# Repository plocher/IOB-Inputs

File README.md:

# IOB-Inputs
## License: CERN Open Hardware Licence v1.2

1k series resistor protects from shorts to Vcc or GND

PNP Ready: Panelized IOB quad "input board", used for [IO4-QuodOD](/pages/IO4-QuadOD), [IO4-IR-Detector-Active](/pages/IO4-IR-Detector-Active), and [IO4-IR-Detector-GBunza](/pages/IO4-IR-Detector-GBunza) detectors as well as other IO4 sensor accessories that provide 4x lines of active-low digital feedback.

  * pin 1: 5vDC
  * pin 2: !IN1
  * pin 3: !IN2
  * pin 4: !IN3
  * pin 5: !IN4
  * pin 6: GND

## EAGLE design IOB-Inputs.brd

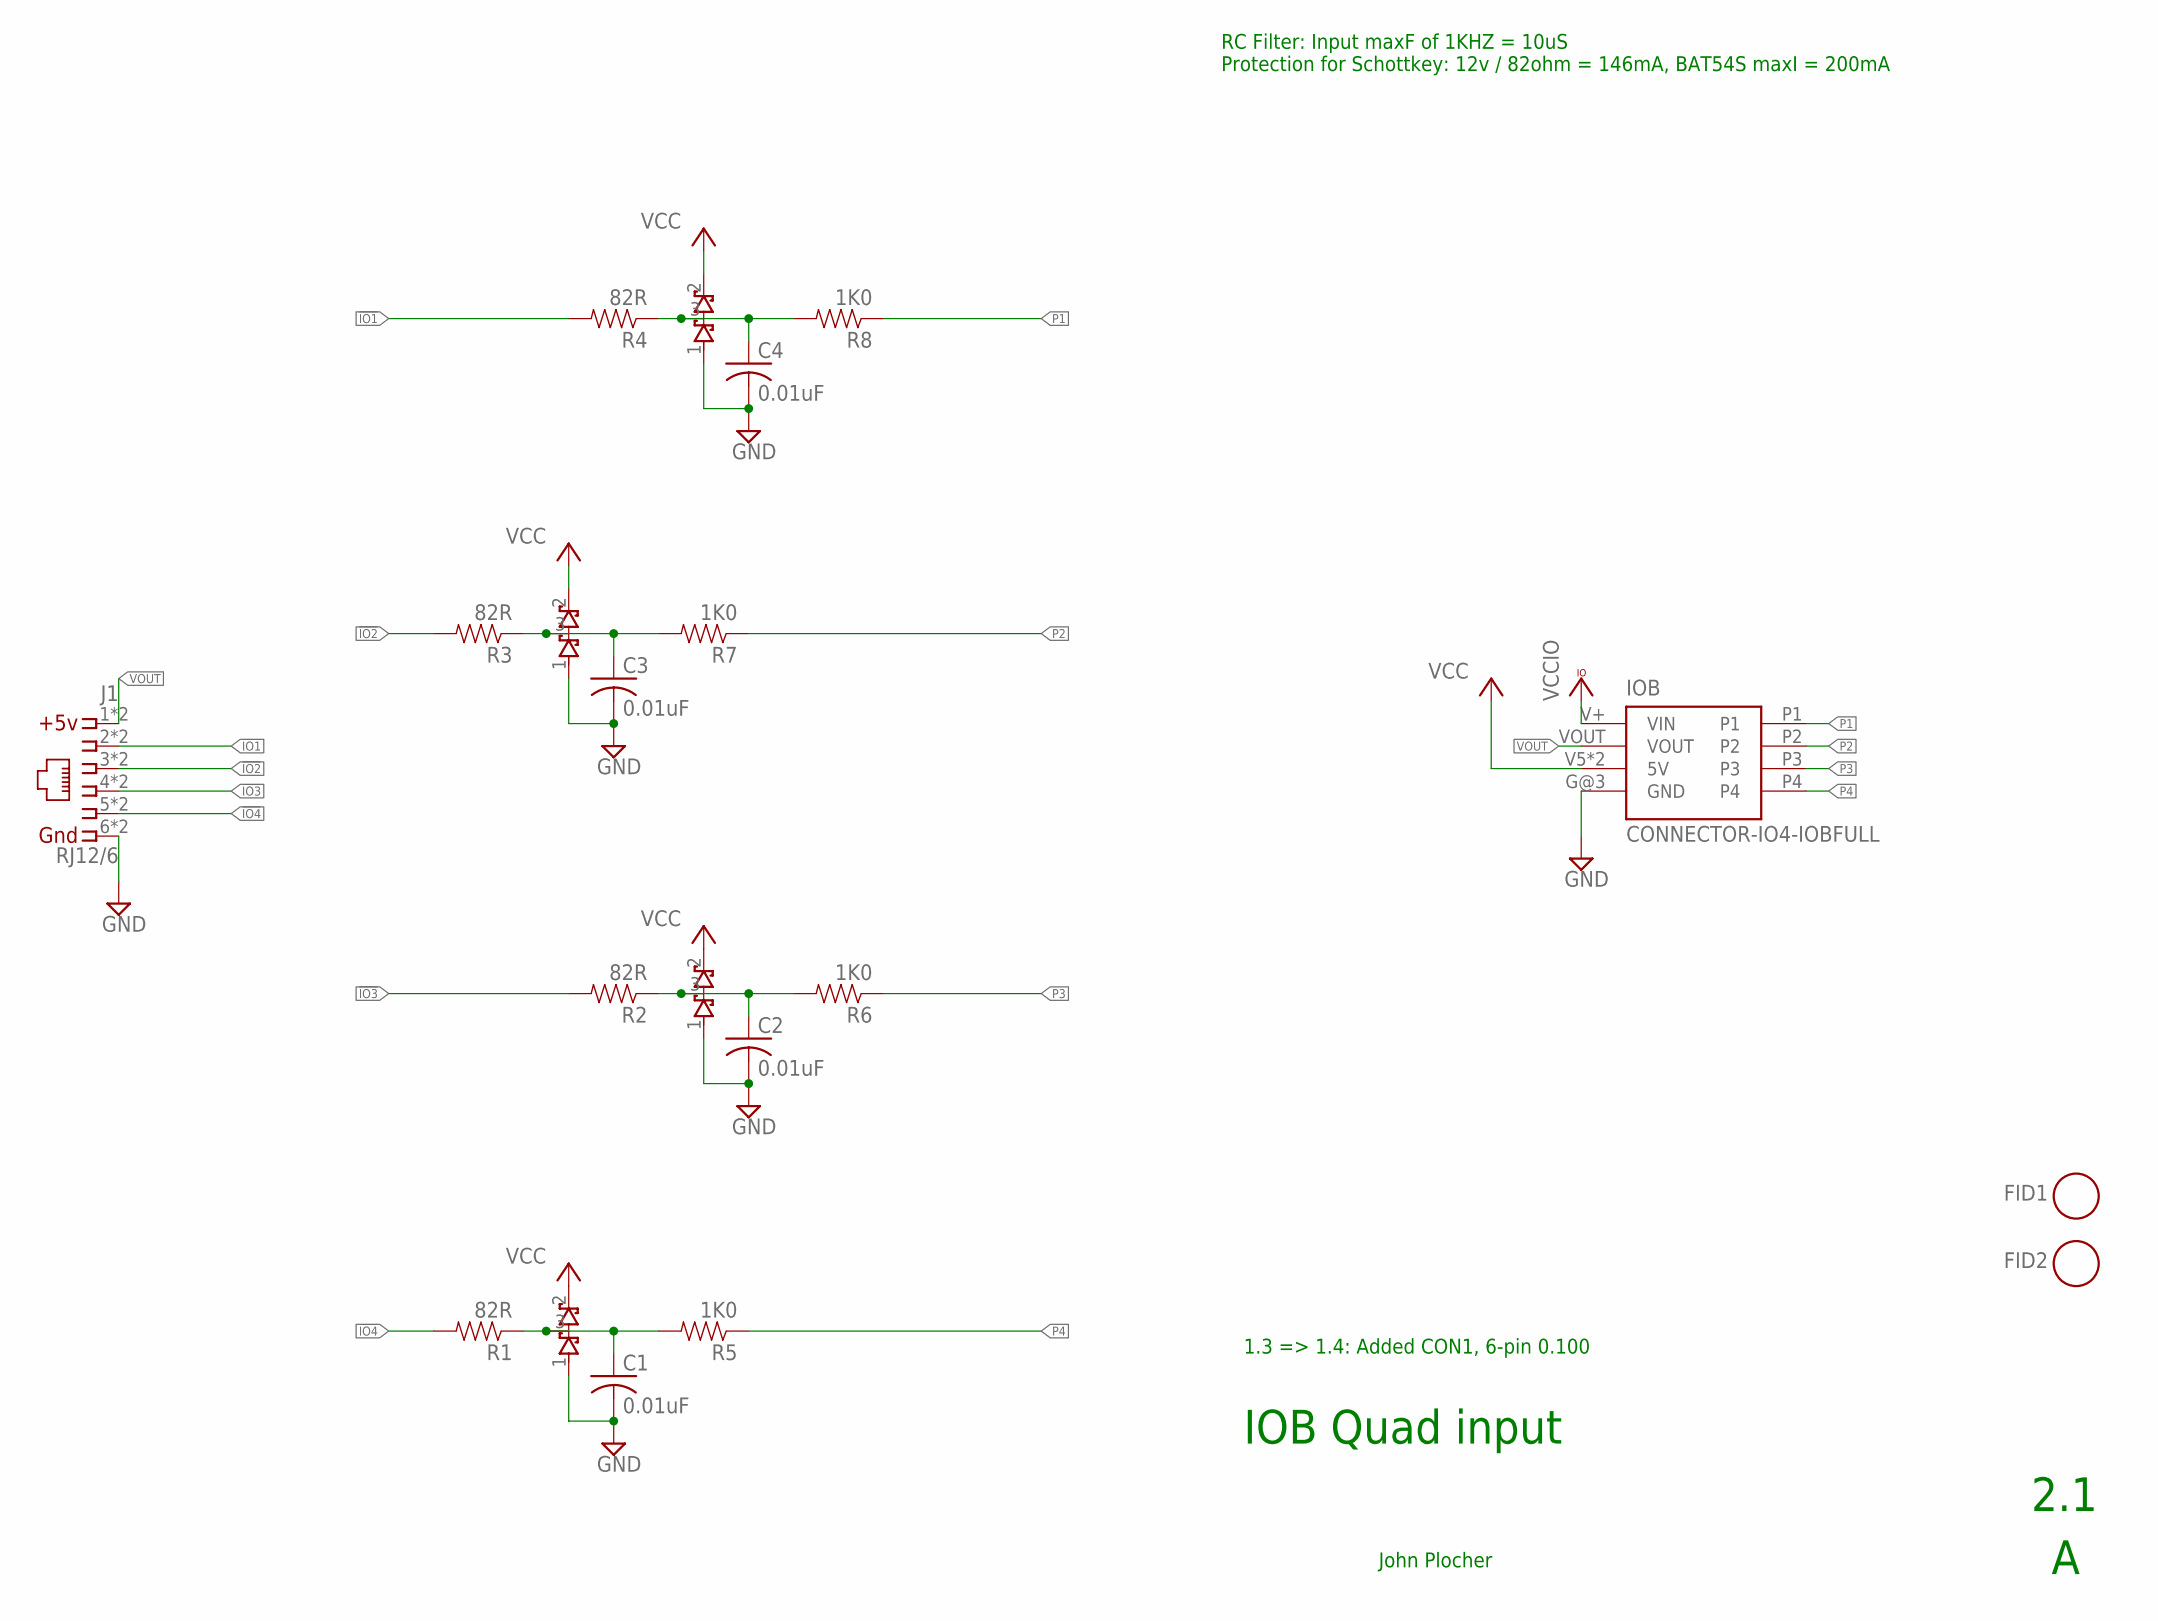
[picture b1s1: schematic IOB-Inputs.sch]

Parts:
C1, C2, C3, C4: 0.01uF; 0603-CAP
D1, D2, D3, D4: BAT54S; SOT23
FID1, FID2: FIDUCIAL; FIDUCIAL_1MM
IOB: CONNECTOR-IO4-IOBFULL; IO4-IOB
J1: RJ12/6; RJ24-INVERTED-PINS
R1, R2, R3, R4: 82R; 0805-RES
R5, R6, R7, R8: 1K0; 0603-RES

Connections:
!IO1: J1.2, J1.2@1 (2), R4.2
!IO2: J1.3, J1.3@1 (3), R3.2
!IO3: J1.4, J1.4@1 (4), R2.2
!IO4: J1.5, J1.5@1 (5), R1.2
GND: C1.2, C2.2, C3.2, C4.2, D1.1 (A1), D2.1 (A1), D3.1 (A1), D4.1 (A1), IOB.G@3 (GND), J1.6, J1.6@1 (6)
unnamed: C1.1, D1.3 (COM), R1.1, R5.2
unnamed: C2.1, D2.3 (COM), R2.1, R6.2
unnamed: C3.1, D3.3 (COM), R3.1, R7.2
unnamed: C4.1, D4.3 (COM), R4.1, R8.2
P1: IOB.P1, R8.1
P2: IOB.P2, R7.1
P3: IOB.P3, R6.1
P4: IOB.P4, R5.1
VCC: D1.2 (C2), D2.2 (C2), D3.2 (C2), D4.2 (C2), IOB.V5 (5V), IOB.V5@1 (5V)
VCCIO: IOB.V+ (VIN)
VOUT: IOB.VOUT, J1.1, J1.1@1 (1)

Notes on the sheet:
IOB Quad input
2.1
RC Filter: Input maxF of 1KHZ = 10uS Protection for Schottkey: 12v / 82ohm = 146mA, BAT54S maxI = 200mA
John Plocher
1.3 => 1.4: Added CON1, 6-pin 0.100

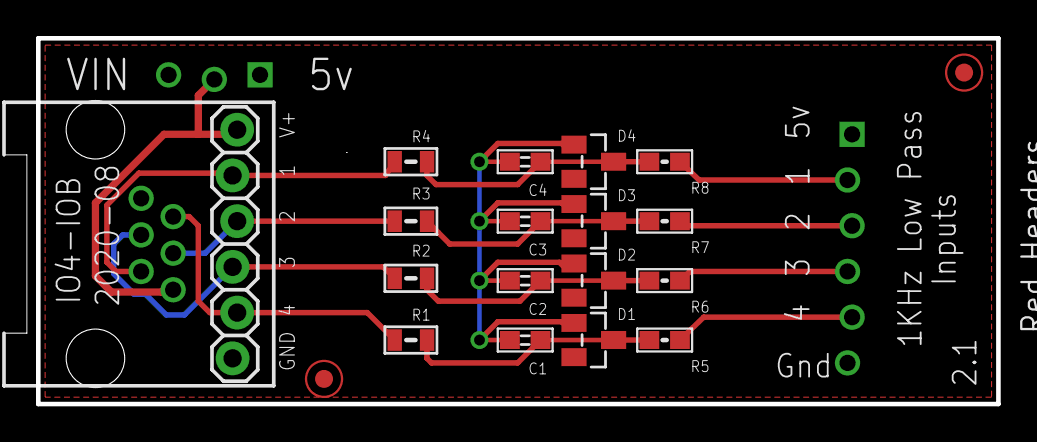
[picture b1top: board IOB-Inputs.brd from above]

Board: 2 copper layers, 53.3 x 20.3 mm, 20 parts (0 on the bottom side), 15 nets.

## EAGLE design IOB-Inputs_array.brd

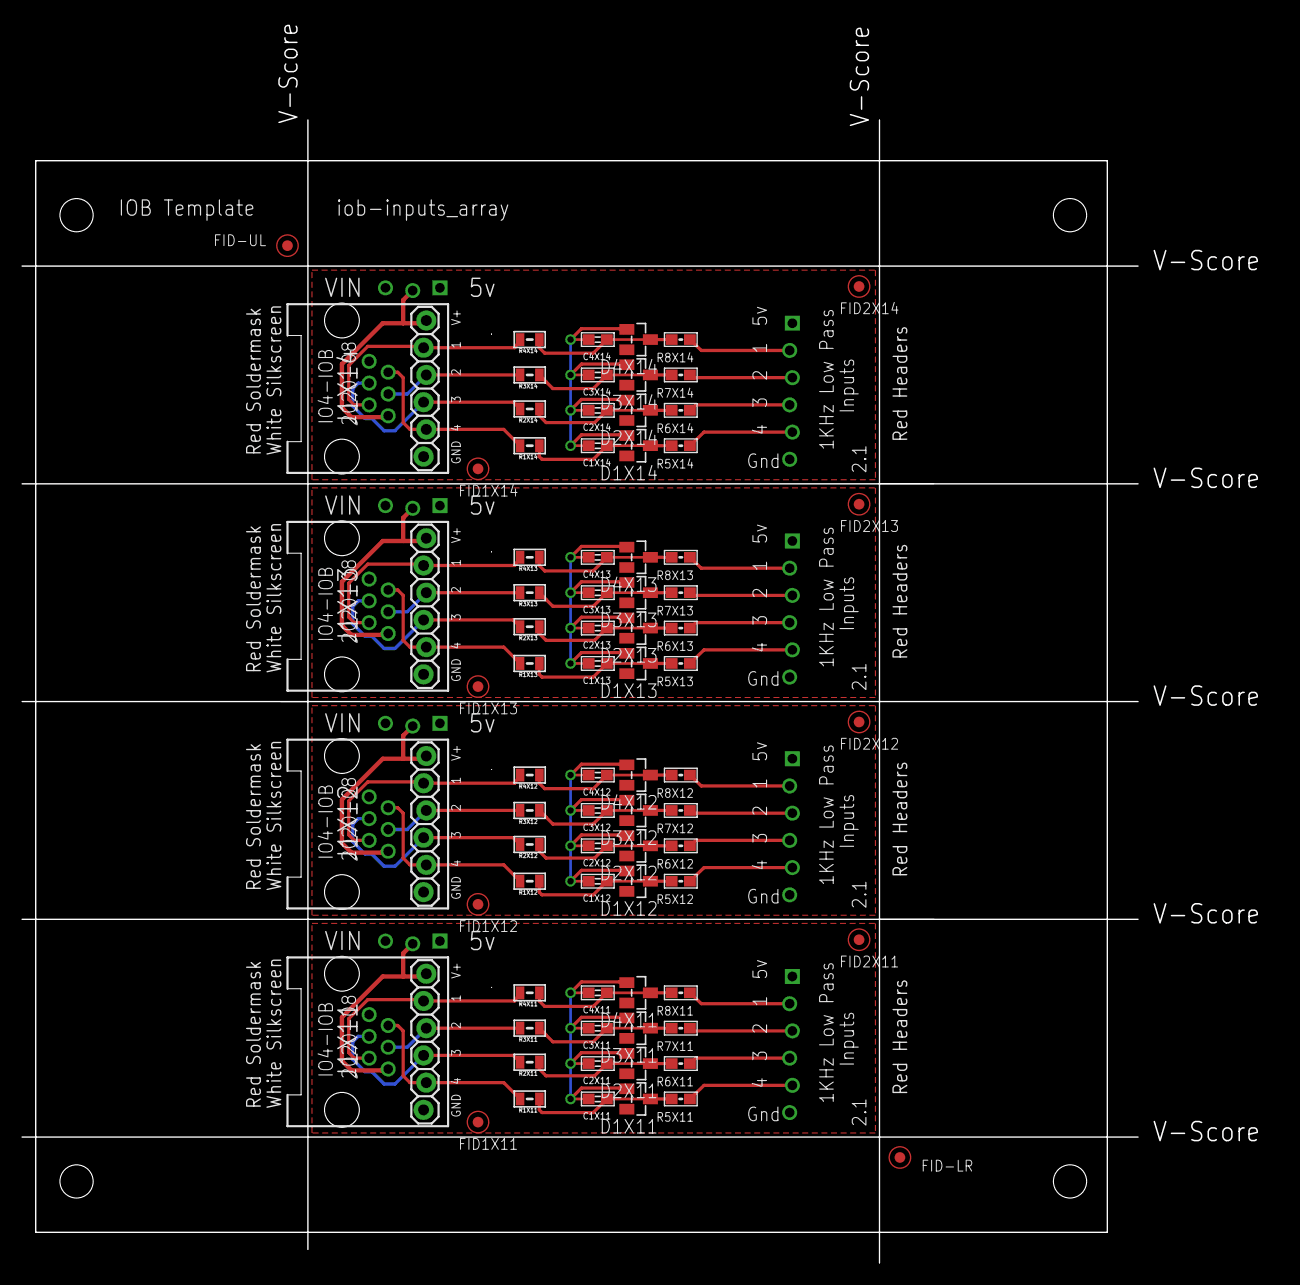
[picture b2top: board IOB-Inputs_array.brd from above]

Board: 2 copper layers, 117.2 x 115.8 mm, 83 parts (0 on the bottom side), 60 nets.

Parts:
C1X11, C1X12, C1X13, C1X14, C2X11, C2X12, C2X13, C2X14, C3X11, C3X12, C3X13, C3X14, C4X11, C4X12, C4X13, C4X14: 0.01uF; 0603-CAP
D1X11, D1X12, D1X13, D1X14, D2X11, D2X12, D2X13, D2X14, D3X11, D3X12, D3X13, D3X14, D4X11, D4X12, D4X13, D4X14: BAT54S; SOT23
FID1X11, FID1X12, FID1X13, FID1X14, FID2X11, FID2X12, FID2X13, FID2X14: FIDUCIAL; FIDUCIAL_1MM
FID-LR: FIDUCIAL; FIDUCIAL_1MM
FID-UL: FIDUCIAL; FIDUCIAL_1MM
IOBX11, IOBX12, IOBX13, IOBX14: CONNECTOR-IO4-IOBFULL; IO4-IOB
J1X11, J1X12, J1X13, J1X14: RJ12/6; RJ24-INVERTED-PINS
R1X11, R1X12, R1X13, R1X14, R2X11, R2X12, R2X13, R2X14, R3X11, R3X12, R3X13, R3X14, R4X11, R4X12, R4X13, R4X14: 82R; 0805-RES
R5X11, R5X12, R5X13, R5X14, R6X11, R6X12, R6X13, R6X14, R7X11, R7X12, R7X13, R7X14, R8X11, R8X12, R8X13, R8X14: 1K0; 0603-RES
R8X1: BOARD-DINRAIL-3.17IN-H4X-IOB

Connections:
!IO1X11: J1X11.2, J1X11.2@1, R4X11.2
!IO1X12: J1X12.2, J1X12.2@1, R4X12.2
!IO1X13: J1X13.2, J1X13.2@1, R4X13.2
!IO1X14: J1X14.2, J1X14.2@1, R4X14.2
!IO2X11: J1X11.3, J1X11.3@1, R3X11.2
!IO2X12: J1X12.3, J1X12.3@1, R3X12.2
!IO2X13: J1X13.3, J1X13.3@1, R3X13.2
!IO2X14: J1X14.3, J1X14.3@1, R3X14.2
!IO3X11: J1X11.4, J1X11.4@1, R2X11.2
!IO3X12: J1X12.4, J1X12.4@1, R2X12.2
!IO3X13: J1X13.4, J1X13.4@1, R2X13.2
!IO3X14: J1X14.4, J1X14.4@1, R2X14.2
!IO4X11: J1X11.5, J1X11.5@1, R1X11.2
!IO4X12: J1X12.5, J1X12.5@1, R1X12.2
!IO4X13: J1X13.5, J1X13.5@1, R1X13.2
!IO4X14: J1X14.5, J1X14.5@1, R1X14.2
GNDX11: C1X11.2, C2X11.2, C3X11.2, C4X11.2, D1X11.1, D2X11.1, D3X11.1, D4X11.1, IOBX11.G@3, J1X11.6, J1X11.6@1
GNDX12: C1X12.2, C2X12.2, C3X12.2, C4X12.2, D1X12.1, D2X12.1, D3X12.1, D4X12.1, IOBX12.G@3, J1X12.6, J1X12.6@1
GNDX13: C1X13.2, C2X13.2, C3X13.2, C4X13.2, D1X13.1, D2X13.1, D3X13.1, D4X13.1, IOBX13.G@3, J1X13.6, J1X13.6@1
GNDX14: C1X14.2, C2X14.2, C3X14.2, C4X14.2, D1X14.1, D2X14.1, D3X14.1, D4X14.1, IOBX14.G@3, J1X14.6, J1X14.6@1
unnamed: C1X11.1, D1X11.3, R1X11.1, R5X11.2
unnamed: C1X12.1, D1X12.3, R1X12.1, R5X12.2
unnamed: C1X13.1, D1X13.3, R1X13.1, R5X13.2
unnamed: C1X14.1, D1X14.3, R1X14.1, R5X14.2
unnamed: C2X11.1, D2X11.3, R2X11.1, R6X11.2
unnamed: C2X12.1, D2X12.3, R2X12.1, R6X12.2
unnamed: C2X13.1, D2X13.3, R2X13.1, R6X13.2
unnamed: C2X14.1, D2X14.3, R2X14.1, R6X14.2
unnamed: C3X11.1, D3X11.3, R3X11.1, R7X11.2
unnamed: C3X12.1, D3X12.3, R3X12.1, R7X12.2
unnamed: C3X13.1, D3X13.3, R3X13.1, R7X13.2
unnamed: C3X14.1, D3X14.3, R3X14.1, R7X14.2
unnamed: C4X11.1, D4X11.3, R4X11.1, R8X11.2
unnamed: C4X12.1, D4X12.3, R4X12.1, R8X12.2
unnamed: C4X13.1, D4X13.3, R4X13.1, R8X13.2
unnamed: C4X14.1, D4X14.3, R4X14.1, R8X14.2
P1X11: IOBX11.P1, R8X11.1
P1X12: IOBX12.P1, R8X12.1
P1X13: IOBX13.P1, R8X13.1
P1X14: IOBX14.P1, R8X14.1
P2X11: IOBX11.P2, R7X11.1
P2X12: IOBX12.P2, R7X12.1
P2X13: IOBX13.P2, R7X13.1
P2X14: IOBX14.P2, R7X14.1
P3X11: IOBX11.P3, R6X11.1
P3X12: IOBX12.P3, R6X12.1
P3X13: IOBX13.P3, R6X13.1
P3X14: IOBX14.P3, R6X14.1
P4X11: IOBX11.P4, R5X11.1
P4X12: IOBX12.P4, R5X12.1
P4X13: IOBX13.P4, R5X13.1
P4X14: IOBX14.P4, R5X14.1
VCCX11: D1X11.2, D2X11.2, D3X11.2, D4X11.2, IOBX11.V5, IOBX11.V5@1
VCCX12: D1X12.2, D2X12.2, D3X12.2, D4X12.2, IOBX12.V5, IOBX12.V5@1
VCCX13: D1X13.2, D2X13.2, D3X13.2, D4X13.2, IOBX13.V5, IOBX13.V5@1
VCCX14: D1X14.2, D2X14.2, D3X14.2, D4X14.2, IOBX14.V5, IOBX14.V5@1
VOUTX11: IOBX11.VOUT, J1X11.1, J1X11.1@1
VOUTX12: IOBX12.VOUT, J1X12.1, J1X12.1@1
VOUTX13: IOBX13.VOUT, J1X13.1, J1X13.1@1
VOUTX14: IOBX14.VOUT, J1X14.1, J1X14.1@1

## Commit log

2019-11-26 spelling
2019-12-09 added graphic
2019-12-19 added input protection diodes and RC filter to handle 1khz or less signals
2019-12-19 Add note re: schottkey & RC filter
2019-12-19 Panelized
2020-01-25 added 6x1 0.100 header
2020-01-25 added 1x6 0.100 header
2020-03-06 new IOB design
2020-03-06 built panelized array
2020-03-07 updated changelog
2020-04-15 updated to use SPCoast colors and layers
2020-05-04 updated tags
2020-08-08 fixed SPCoast.lbr diode orientation
2020-08-09 Added missing values
2020-08-09 Replaced too small BAT54S SOT23R footprint with SOT23
2020-08-09 Rev to 2.1 because of Stencil change
2020-08-11 normalized silkscreen layout across IOBs
2020-08-11 move text from DOCU to TPLACE
2020-08-11 SPCoast Color Pallette
2020-08-11 Moved 82R inline with others
2020-09-12 test
